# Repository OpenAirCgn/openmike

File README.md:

# Breakout for ICS43434 MEMS i2s Microphone

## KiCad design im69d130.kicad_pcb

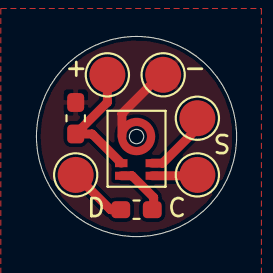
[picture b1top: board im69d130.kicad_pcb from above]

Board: 2 copper layers, 11.1 x 11.1 mm, 8 parts (0 on the bottom side), 6 nets.

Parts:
C1: 100nF; C_0603_1608Metric_Pad1.05x0.95mm_HandSolder
MK1: IM69D130; Infineon_PG-LLGA-5-1
R1: 100; R_0603_1608Metric_Pad1.05x0.95mm_HandSolder
TP1: +; TestPoint_Pad_D2.0mm
TP2: S; TestPoint_Pad_D2.0mm
TP3: C; TestPoint_Pad_D2.0mm
TP4: D; TestPoint_Pad_D2.0mm
TP5: -; TestPoint_Pad_D2.0mm

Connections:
Clock: MK1.3, TP3.1
Data: R1.2, TP4.1
GND: C1.2, MK1.5, TP5.1
unnamed: MK1.1, R1.1
Select: MK1.4, TP2.1
VDD: C1.1, MK1.2, TP1.1

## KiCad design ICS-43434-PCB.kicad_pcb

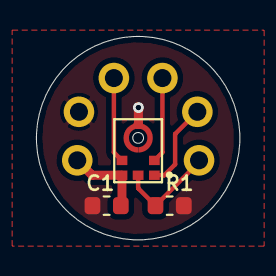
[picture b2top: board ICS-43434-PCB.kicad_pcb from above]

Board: 2 copper layers, 11.3 x 11.3 mm, 9 parts (0 on the bottom side), 6 nets.

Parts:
C1: 100nF; C_0603_1608Metric
MK1: ICS-43434; MIC_ICS-43434
R1: 100K; R_0603_1608Metric
TP1: +; PinHeader_1x01_P2.54mm_Vertical
TP2: SC; PinHeader_1x01_P2.54mm_Vertical
TP3: LR; PinHeader_1x01_P2.54mm_Vertical
TP4: WS; PinHeader_1x01_P2.54mm_Vertical
TP5: SD; PinHeader_1x01_P2.54mm_Vertical
TP6: -; PinHeader_1x01_P2.54mm_Vertical

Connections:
+3V3: C1.1, MK1.5, TP1.1
GND: C1.2, MK1.3, R1.2, TP6.1
LR: MK1.2, TP3.1
SCK: MK1.4, TP2.1
SD: MK1.6, R1.1, TP5.1
WS: MK1.1, TP4.1

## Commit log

2020-02-14 minor adjustments
2020-02-14 initial docs
2020-06-02 initial
